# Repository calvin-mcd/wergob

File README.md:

# wergob

This is a pcb for the ergo board by _obabo called wergob!

## Layout

[Link](https://www.keyboard-layout-editor.com/#/gists/adf7cc06b15a428de764ebef3565cc50)

## Case

_obabo is designing a dedicated case for this unique layout!

## Todo

- [ ] order & test pcb
- [ ] design & test case
- [ ] create firmware

## Disclaimer

Please note that this project is a work in progress with no guarantees of a working outcome. No-one involved in this project is responsible for any usage issues that may arise. However, feel free to edit, modify and otherwise utilise these files.

## License

This project is released under the GPL v3 License. Please refer to the LICENCE file.

## Credits

big thanks to _obabo for the inspiring keyboard designs for our community! 

Any questions, contact Calvin\#0563 on Discord.

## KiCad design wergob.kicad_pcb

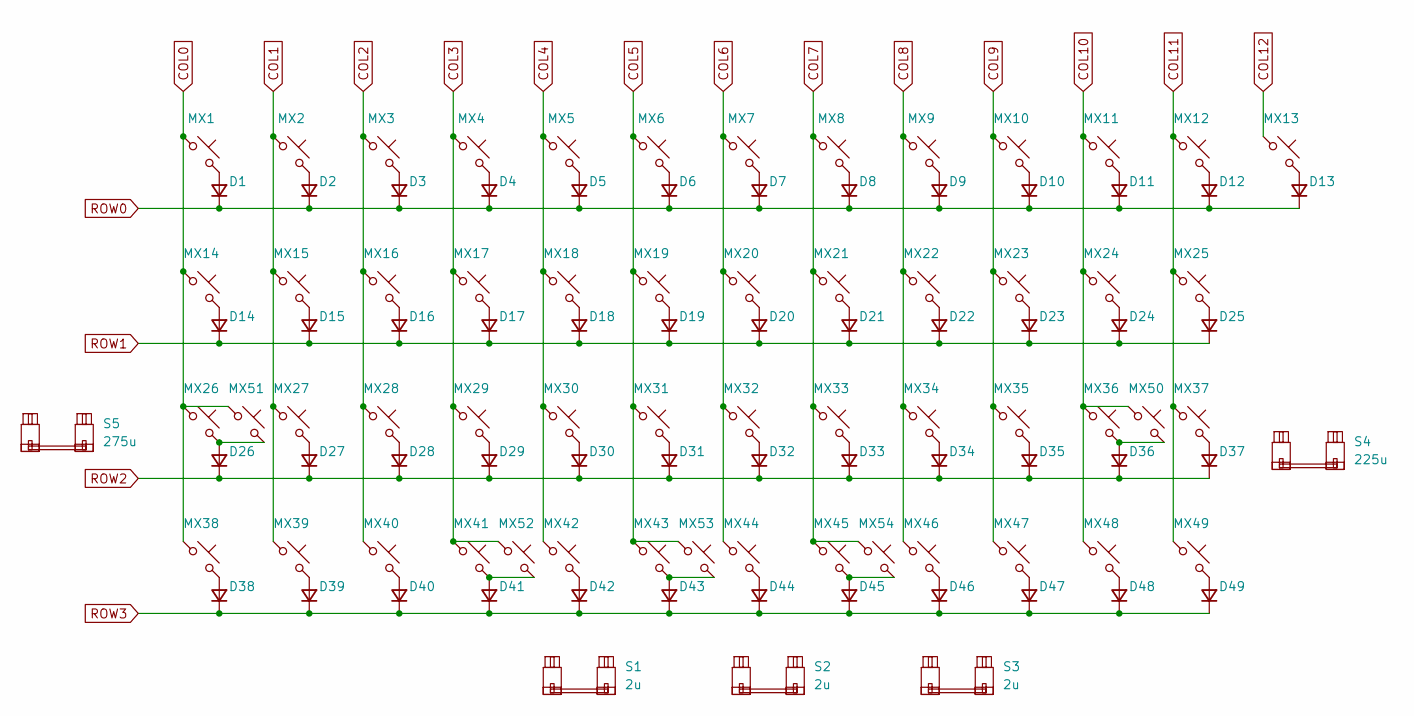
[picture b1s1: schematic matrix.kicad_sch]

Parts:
D1, D2, D3, D4, D5, D6, D7, D8, D9, D10, D11, D12, D13, D14, D15, D16, D17, D18, D19, D20, D21, D22, D23, D24, D25, D26, D27, D28, D29, D30, D31, D32, D33, D34, D35, D36, D37, D38, D39, D40, D41, D42, D43, D44, D45, D46, D47, D48, D49: D_Small; D_SOD-123F
MX1, MX2, MX3, MX4, MX5, MX6, MX7, MX8, MX9, MX10, MX11, MX12, MX13, MX15, MX16, MX17, MX18, MX19, MX20, MX21, MX22, MX23, MX24, MX27, MX28, MX29, MX30, MX31, MX32, MX33, MX34, MX35, MX36, MX38, MX39, MX40, MX41, MX42, MX43, MX44, MX45, MX46, MX47, MX48, MX49, MX50, MX51, MX52, MX53, MX54: MX_SW_solder; SW_MX_1u
MX14, MX37: MX_SW_solder; SW_MX_1.25u
MX25, MX26: MX_SW_solder; SW_MX_1.75u
S1, S2, S3: 2u; STAB_MX_P_2u
S4: 225u; STAB_MX_P_2.25u
S5: 275u; STAB_MX_P_2.75u

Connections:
COL0: MX1.1, MX14.1, MX26.1, MX38.1, MX51.1; also elsewhere on the board
COL1: MX2.1, MX15.1, MX27.1, MX39.1; also elsewhere on the board
COL2: MX3.1, MX16.1, MX28.1, MX40.1; also elsewhere on the board
COL3: MX4.1, MX17.1, MX29.1, MX41.1, MX52.1; also elsewhere on the board
COL4: MX5.1, MX18.1, MX30.1, MX42.1; also elsewhere on the board
COL5: MX6.1, MX19.1, MX31.1, MX43.1, MX53.1; also elsewhere on the board
COL6: MX7.1, MX20.1, MX32.1, MX44.1; also elsewhere on the board
COL7: MX8.1, MX21.1, MX33.1, MX45.1, MX54.1; also elsewhere on the board
COL8: MX9.1, MX22.1, MX34.1, MX46.1; also elsewhere on the board
COL9: MX10.1, MX23.1, MX35.1, MX47.1; also elsewhere on the board
COL10: MX11.1, MX24.1, MX36.1, MX48.1, MX50.1; also elsewhere on the board
COL11: MX12.1, MX25.1, MX37.1, MX49.1; also elsewhere on the board
COL12: MX13.1; also elsewhere on the board
unnamed: D1.2 (A), MX1.2
unnamed: D2.2 (A), MX2.2
unnamed: D3.2 (A), MX3.2
unnamed: D4.2 (A), MX4.2
unnamed: D5.2 (A), MX5.2
unnamed: D6.2 (A), MX6.2
unnamed: D7.2 (A), MX7.2
unnamed: D8.2 (A), MX8.2
unnamed: D9.2 (A), MX9.2
unnamed: D10.2 (A), MX10.2
unnamed: D11.2 (A), MX11.2
unnamed: D12.2 (A), MX12.2
unnamed: D13.2 (A), MX13.2
unnamed: D14.2 (A), MX14.2
unnamed: D15.2 (A), MX15.2
unnamed: D16.2 (A), MX16.2
unnamed: D17.2 (A), MX17.2
unnamed: D18.2 (A), MX18.2
unnamed: D19.2 (A), MX19.2
unnamed: D20.2 (A), MX20.2
unnamed: D21.2 (A), MX21.2
unnamed: D22.2 (A), MX22.2
unnamed: D23.2 (A), MX23.2
unnamed: D24.2 (A), MX24.2
unnamed: D25.2 (A), MX25.2
unnamed: D26.2 (A), MX26.2, MX51.2
unnamed: D27.2 (A), MX27.2
unnamed: D28.2 (A), MX28.2
unnamed: D29.2 (A), MX29.2
unnamed: D30.2 (A), MX30.2
unnamed: D31.2 (A), MX31.2
unnamed: D32.2 (A), MX32.2
unnamed: D33.2 (A), MX33.2
unnamed: D34.2 (A), MX34.2
unnamed: D35.2 (A), MX35.2
unnamed: D36.2 (A), MX36.2, MX50.2
unnamed: D37.2 (A), MX37.2
unnamed: D38.2 (A), MX38.2
unnamed: D39.2 (A), MX39.2
unnamed: D40.2 (A), MX40.2
unnamed: D41.2 (A), MX41.2, MX52.2
unnamed: D42.2 (A), MX42.2
unnamed: D43.2 (A), MX43.2, MX53.2
unnamed: D44.2 (A), MX44.2
unnamed: D45.2 (A), MX45.2, MX54.2
unnamed: D46.2 (A), MX46.2
unnamed: D47.2 (A), MX47.2
unnamed: D48.2 (A), MX48.2
unnamed: D49.2 (A), MX49.2
ROW0: D1.1 (K), D2.1 (K), D3.1 (K), D4.1 (K), D5.1 (K), D6.1 (K), D7.1 (K), D8.1 (K), D9.1 (K), D10.1 (K), D11.1 (K), D12.1 (K), D13.1 (K); also elsewhere on the board
ROW1: D14.1 (K), D15.1 (K), D16.1 (K), D17.1 (K), D18.1 (K), D19.1 (K), D20.1 (K), D21.1 (K), D22.1 (K), D23.1 (K), D24.1 (K), D25.1 (K); also elsewhere on the board
ROW2: D26.1 (K), D27.1 (K), D28.1 (K), D29.1 (K), D30.1 (K), D31.1 (K), D32.1 (K), D33.1 (K), D34.1 (K), D35.1 (K), D36.1 (K), D37.1 (K); also elsewhere on the board
ROW3: D38.1 (K), D39.1 (K), D40.1 (K), D41.1 (K), D42.1 (K), D43.1 (K), D44.1 (K), D45.1 (K), D46.1 (K), D47.1 (K), D48.1 (K), D49.1 (K); also elsewhere on the board

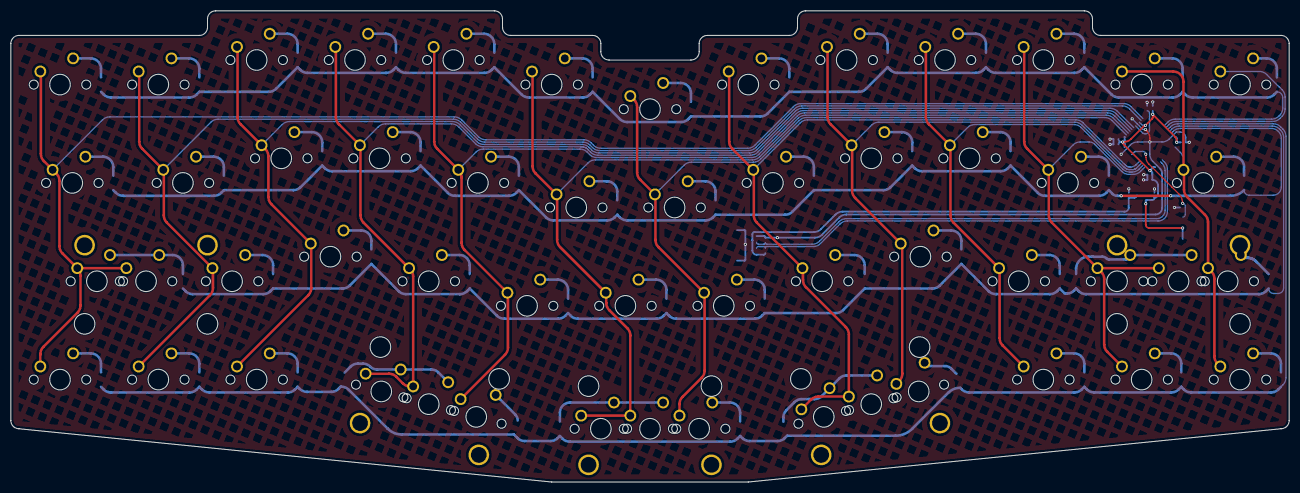
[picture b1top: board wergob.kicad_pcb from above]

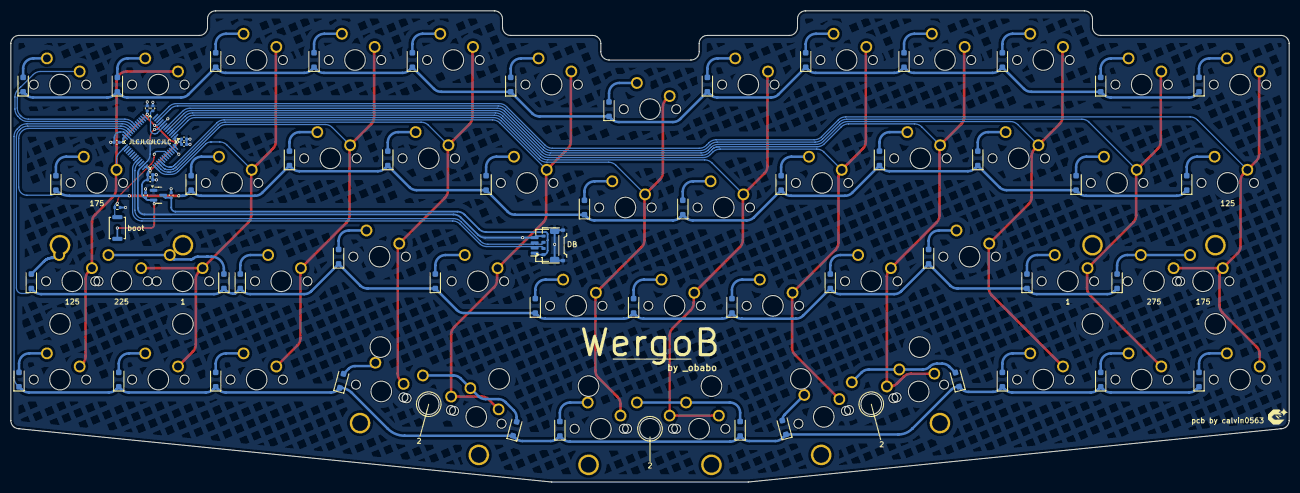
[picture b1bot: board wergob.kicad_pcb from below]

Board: 2 copper layers, 247.6 x 91.3 mm, 123 parts (64 on the bottom side), 73 nets.

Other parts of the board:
C1, C2, C3, C4, C5, C7: 100nF; C_0402_1005Metric
C6: 10uF; C_0402_1005Metric
C8, C9: 1uF; C_0402_1005Metric
J1: JST SH; JST_SH_SM04B-SRSS-TB_1x04-1MP_P1.00mm_Horizontal
J2: Pico EZmate; Molex_Pico-EZmate_78171-0004_1x04-1MP_P1.20mm_Vertical
R1: 10k; R_0402_1005Metric
SW1: SKQGABE010; SW_Push_SPST_NO_Alps_SKRK
U1: STM32F072CBT6; LQFP-48_7x7mm_P0.5mm
U2: XC6206PxxxMR-Regulator_Linear; SOT-23

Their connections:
+3V3: C1.1, C2.1, C3.1, C4.1, C5.1, C6.1, C9.2, SW1.1, U1.1 (VBAT), U1.9 (VDDA), U1.24 (VDD), U1.36 (VDDIO2), U1.48 (VDD), U2.2 (VO)
+5V: C8.2, J1.1, J2.1, U2.3 (VI)
BOOT0: R1.1, SW1.2, U1.44 (BOOT0)
COL0: U1.11 (PA1); also elsewhere on the board
COL1: U1.10 (PA0); also elsewhere on the board
COL2: U1.6 (PF1); also elsewhere on the board
COL3: U1.5 (PF0); also elsewhere on the board
COL4: U1.4 (PC15); also elsewhere on the board
COL5: U1.3 (PC14); also elsewhere on the board
COL6: U1.2 (PC13); also elsewhere on the board
COL7: U1.40 (PB4); also elsewhere on the board
COL8: U1.39 (PB3); also elsewhere on the board
COL9: U1.38 (PA15); also elsewhere on the board
COL10: U1.37 (PA14); also elsewhere on the board
COL11: U1.25 (PB12); also elsewhere on the board
COL12: U1.19 (PB1); also elsewhere on the board
D_N: J1.2, J2.2, U1.32 (PA11)
D_P: J1.3, J2.3, U1.33 (PA12)
GND: C1.2, C2.2, C3.2, C4.2, C5.2, C6.2, C7.2, C8.1, C9.1, J1.4, J1.MP (MountPin), J2.4, J2.MP (MountPin), R1.2, U1.8 (VSSA), U1.23 (VSS), U1.35 (VSS), U1.47 (VSS), U2.1 (GND)
NRST: C7.1, U1.7 (NRST)
ROW0: U1.18 (PB0); also elsewhere on the board
ROW1: U1.22 (PB11); also elsewhere on the board
ROW2: U1.21 (PB10); also elsewhere on the board
ROW3: U1.20 (PB2); also elsewhere on the board

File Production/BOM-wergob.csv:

Comment,Designator,Footprint,LCSC,Quantity
10uF,C6,C_0402_1005Metric,C15525,1
JST SH,J1,JST_SH_SM04B-SRSS-TB_1x04-1MP_P1.00mm_Horizontal,C160404,1
10k,R1,R_0402_1005Metric,C25744,1
100nF,"C1,C2,C3,C4,C5,C7",C_0402_1005Metric,C307331,6
1uF,"C8,C9",C_0402_1005Metric,C52923,2
XC6206PxxxMR-Regulator_Linear,U2,SOT-23,C5446,1
SKQGABE010,SW1,SW_Push_SPST_NO_Alps_SKRK,C561519,1
D_Small,"D1,D10,D11,D12,D13,D14,D15,D16,D17,D18,D19,D2,D20,D21,D22,D23,D24,D25,D26,D27,D28,D29,D3,D30,D31,D32,D33,D34,D35,D36,D37,D38,D39,D4,D40,D41,D42,D43,D44,D45,D46,D47,D48,D49,D5,D6,D7,D8,D9",D_SOD-123F,C64898,49
STM32F072CBT6,U1,LQFP-48_7x7mm_P0.5mm,C80488,1

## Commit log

2025-03-15 project initialised
